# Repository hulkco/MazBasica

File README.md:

# MazBasica v1.0
Arduino UNO trainer shield.
Source code as included in Ardublock, which is a visual programming language, which will enable students ages 8 and up, marvelous introduction to the world of programming and physical computing.
/////
Tarjeta entrenadora para Arduino UNO.
Se incluye código fuente en Ardublock, el cual es un lenguaje de programacion visual, el cual permitira a los alumnos de 8 años en adelante, introducirse al maravillos mundo de la programacion y la computacion fisica.

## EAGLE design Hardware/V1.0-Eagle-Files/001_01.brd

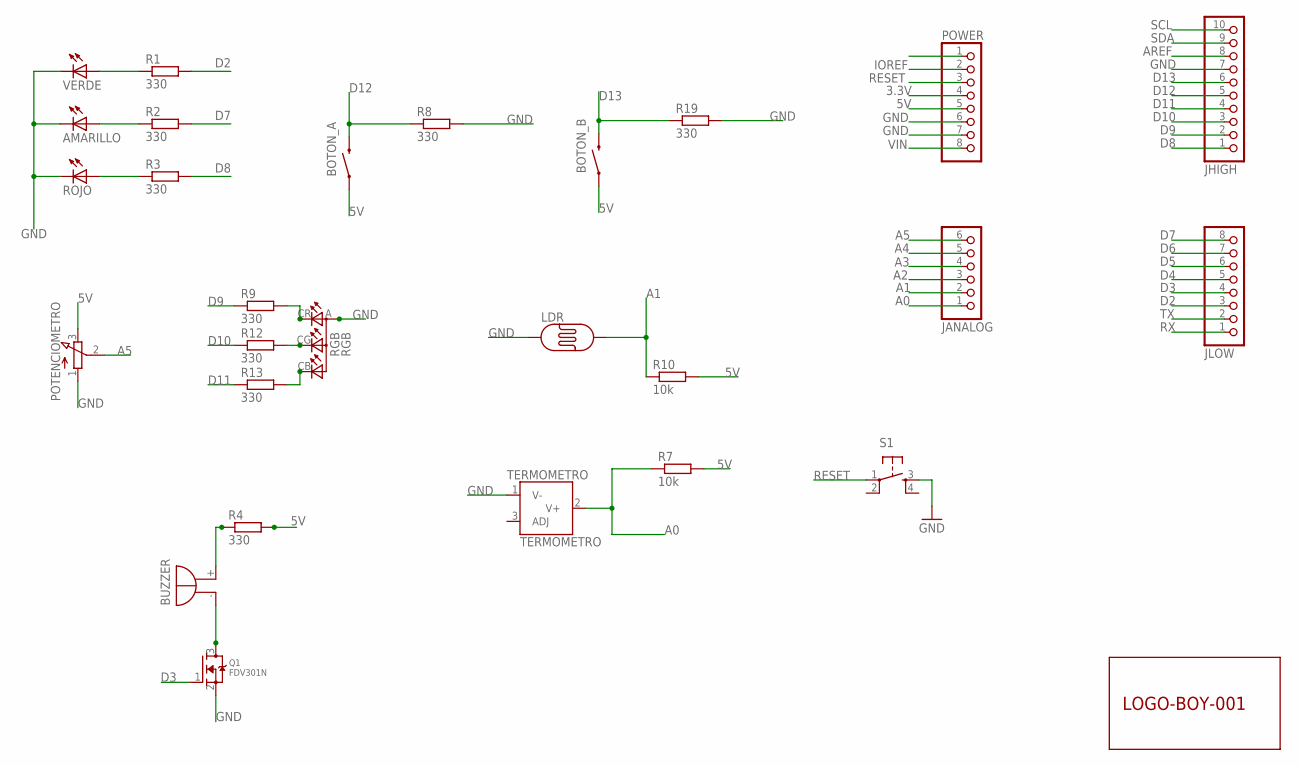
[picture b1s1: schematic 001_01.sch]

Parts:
AMARILLO: LED10MM
BOTON_A: SWITCH-MOMENTARY-212MM; TACTILE-PTH-12MM
BOTON_B: SWITCH-MOMENTARY-212MM; TACTILE-PTH-12MM
BUZZER: BUZZER; F/QMBIII
JANALOG: 6x1F-H8.5-L14.5mm; 1X06-TH
JHIGH: 10x1F-H8.5-L14.5mm; 1X10-TH
JLOW: 8x1F-H8.5-L14.5mm; 1X08-TH
LDR: FOTOCELDA; PHOTOCELL
POTENCIOMETRO: POTENCIOMETRO; EVUF
POWER: 8x1F-H8.5-L14.5mm; 1X08-TH
Q1: FDV301N; SOT23-W
R1, R2, R3, R4, R8, R9, R12, R13, R19: 330; M1206
R7, R10: 10k; M1206
RGB: RGB; LED-RGB-10MM
ROJO: LED10MM
S1: TAC_SWITCHSMD; TACTILE_SWITCH_SMD
TERMOMETRO: TERMOMETRO; LM335Z
U$1: LOGO-BOY-001
VERDE: LED10MM

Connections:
3.3V: POWER.4
5V: BOTON_A.1, BOTON_B.1, POTENCIOMETRO.3 (E), POWER.5, R4.2, R7.2, R10.2
A0: JANALOG.1, R7.1, TERMOMETRO.2 (V+)
A1: JANALOG.2, LDR.2, R10.1
A2: JANALOG.3
A3: JANALOG.4
A4: JANALOG.5
A5: JANALOG.6, POTENCIOMETRO.2 (S)
AREF: JHIGH.8
D2: JLOW.3, R1.2
D3: JLOW.4, Q1.1 (G)
D4: JLOW.5
D5: JLOW.6
D6: JLOW.7
D7: JLOW.8, R2.2
D8: JHIGH.1, R3.2
D9: JHIGH.2, R9.1
D10: JHIGH.3, R12.1
D11: JHIGH.4, R13.1
D12: BOTON_A.3 (2), JHIGH.5, R8.1
D13: BOTON_B.3 (2), JHIGH.6, R19.1
GND: AMARILLO.K (C), JHIGH.7, LDR.1, POTENCIOMETRO.1 (A), POWER.6, POWER.7, Q1.2 (S), R8.2, R19.2, RGB.A, ROJO.K (C), S1.3, TERMOMETRO.1 (V-), VERDE.K (C)
IOREF: POWER.2
unnamed: R9.2, RGB.CR
unnamed: R12.2, RGB.CG
unnamed: R13.2, RGB.CB
unnamed: BUZZER.+ (-), R4.1
unnamed: R1.1, VERDE.A
unnamed: AMARILLO.A, R2.1
unnamed: R3.1, ROJO.A
unnamed: BUZZER.- (+), Q1.3 (D)
RESET: POWER.3, S1.1
RX: JLOW.1
SCL: JHIGH.10
SDA: JHIGH.9
TX: JLOW.2
VIN: POWER.8

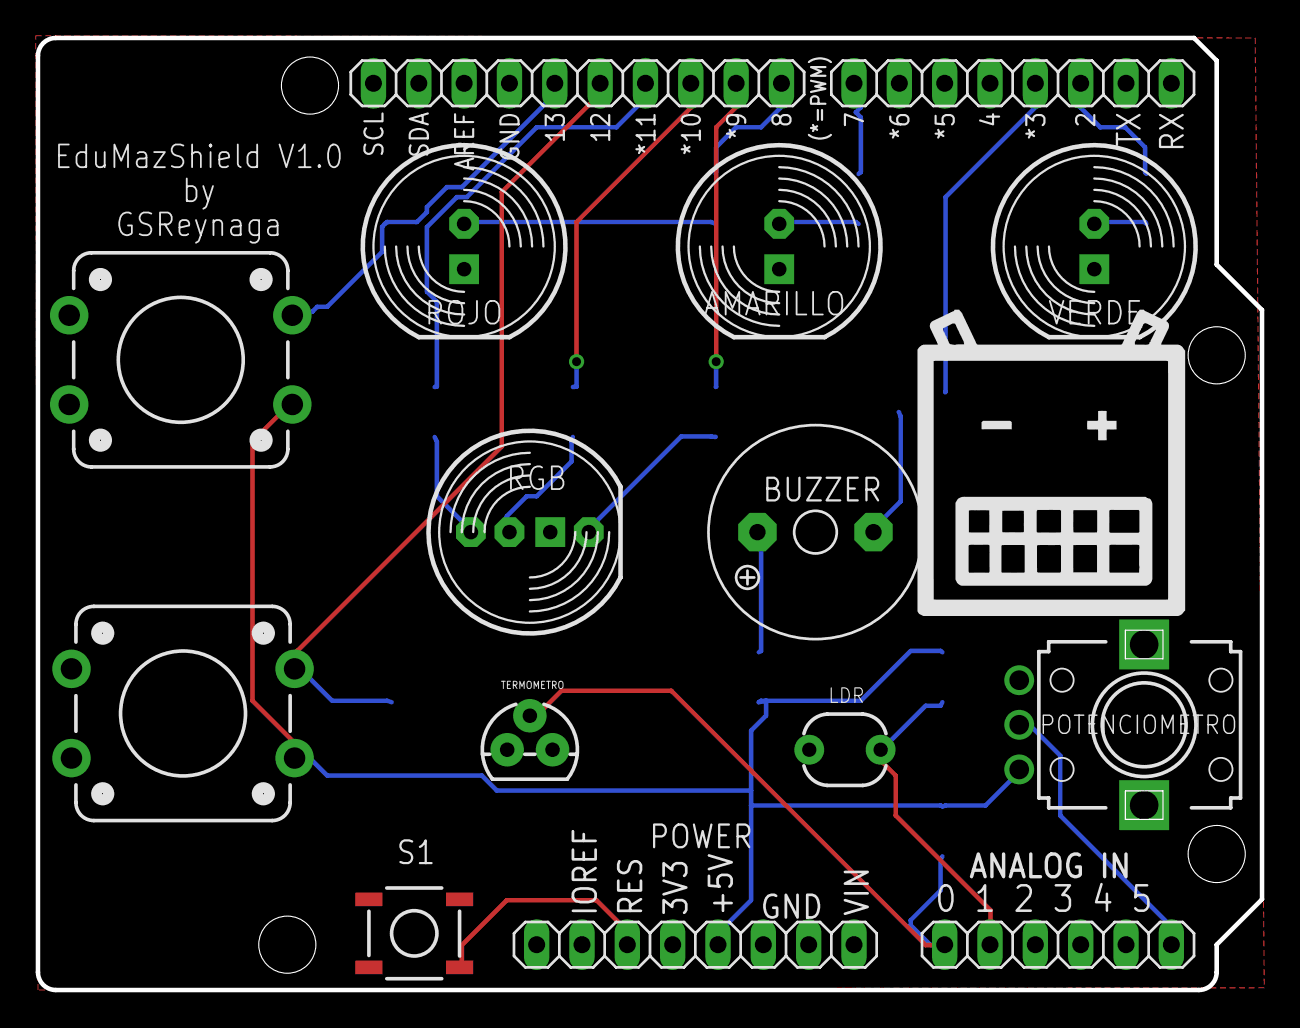
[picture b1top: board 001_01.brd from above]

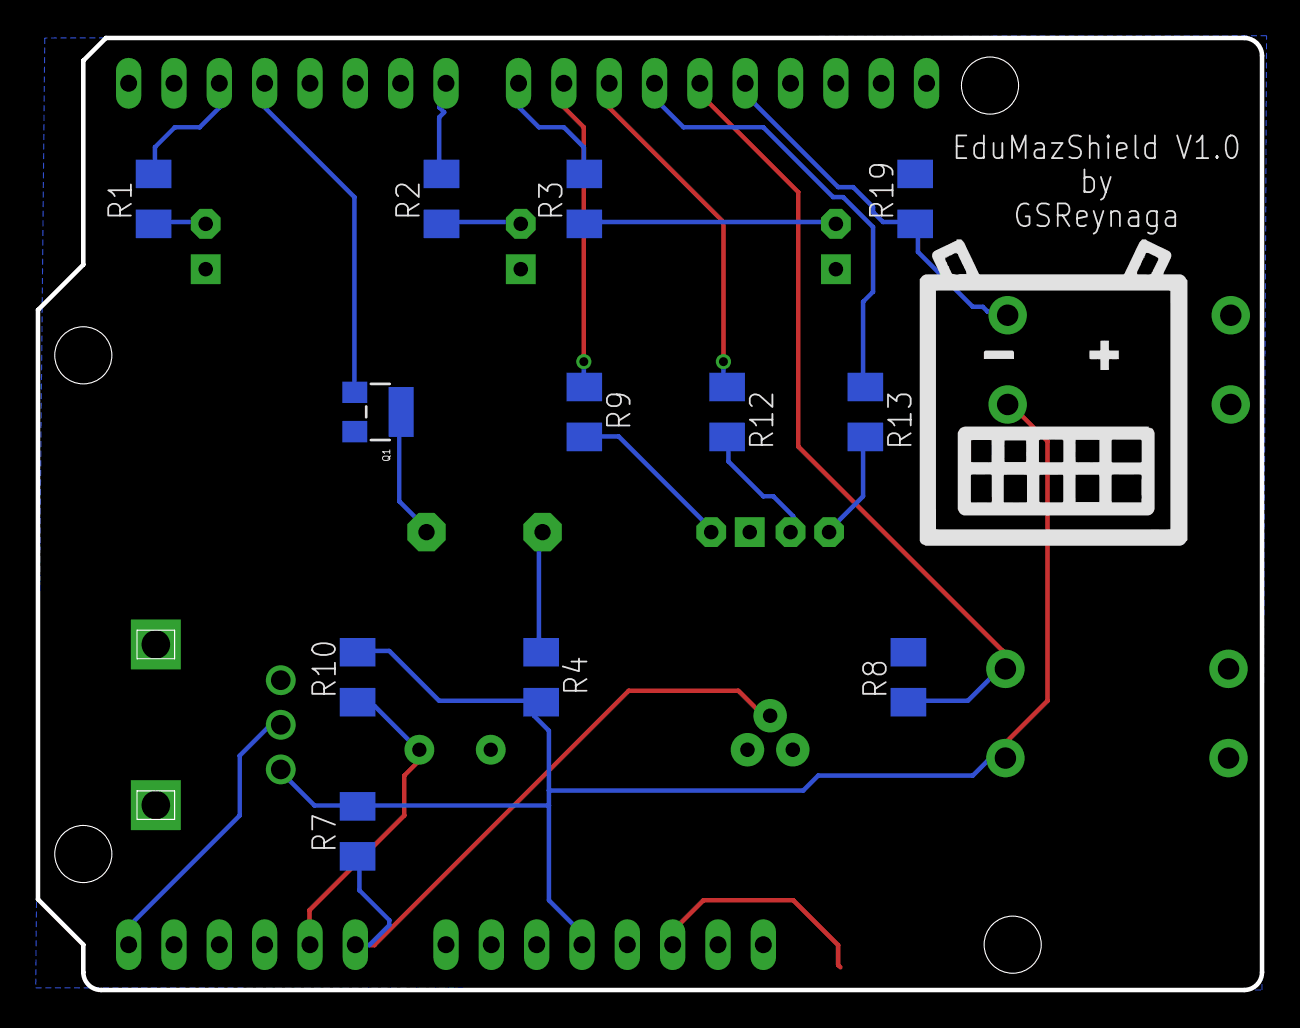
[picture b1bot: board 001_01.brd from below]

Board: 2 copper layers, 68.6 x 53.3 mm, 29 parts (13 on the bottom side), 23 nets.

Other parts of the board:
U$2: LOGO-BOY-001

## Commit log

2015-12-23 Comentario
2015-12-23 Fotos
2015-12-26 Create gh-pages branch via GitHub
2016-02-25 Cambio estructura
2016-05-18 Create todo
2017-06-12 Changes 16-06-2017
    Minor changes to manual.
2017-06-12 Changes file name
    Update the file name
2017-06-12 Change Directory Name
2019-02-21 Update KiCad Files

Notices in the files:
parts and their libraries:
SparkFun-Electromechanical: Licensing: Creative Commons ShareAlike 4.0 International - https://creativecommons.org/licenses/by-sa/4.0
